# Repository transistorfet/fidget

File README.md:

Fidget - The FPGA Widget
========================

###### *Started January 5, 2023*

This project is an experiment in making a board using a Lattice iCE40 FPGA in a surface mount
package (LQFP-144).  It has bus connectors to allow it to be hooked up to one of the
[Computie](https://jabberwocky.ca/projects/computie/) single board computers, to be used as either a
debug monitor to replace the arduino supervisor, or as a generic expansion device for the computers.
I'd also like to be able to use it more generically as well, for example as a logic analyzer, which
is why it's called a widget.

It needs to have bus transceivers to level convert between the 5V signals of the Computie expansion
bus, and the 3.3V I/O pins of the FPGA.  To save on I/Os, the address and data bus lines are
multiplexed using the level-converting transceivers.  I also added the latches necessary to make a
request on the bus.  Without the latches, the device will only be able to receive bus requests but
not make them.

The basic design of the USB and power supply circuitry was mostly copied from the [TinyFPGA
BX](https://www.crowdsupply.com/tinyfpga/tinyfpga-ax-bx) development board.  I bought one back in
early 2020, and have an environment set up for developing for it.  I was able to reuse the
bootloader and upload utility from that to accelerate the bring-up of this board.  I highly
recommend checking it out, especially since it sounds like they will have more boards for sale soon
in 2023.  It's an excellent affordable open source board which is great for experimenting with
verilog and FPGAs.

The schematics can be seen online
[here](https://github.com/transistorfet/fidget/blob/main/hardware/Fidget/Fidget.pdf) or in KiCAD.

This repository uses submodules, and can be cloned using:
```
git clone --recurse-submodules git@github.com:transistorfet/fidget.git
```

Building the Board
------------------

It was surprisingly easy to build, although my attempts at documenting the soldering of the
transceivers resulted in more mistakes than it was worth.  I had solder bridges on every chip that
required some solder wick, and I had a few chips that were crooked enough that I decided to just use
the hot air rework station to remove them and resolder them.  The FPGA was actually much easier to
solder by comparison.  The other parts I had trouble with were the oscillators, which come in a
module on a tiny circuit board with castellated pins on the edges.  The 3.6864 Mhz one was easy
because the footprint turned out to be way bigger than the chip, but the 16 MHz one was the right
size for the part but with not enough clearance for hand soldering.  In future revisions I'll have
to make the footprint bigger.

I started with the 3.3V regulator and tested it with a bench power supply at 5V to verify that I was
getting 3.3V output, which is used by the transceivers.  I then soldered the transceivers and
latches at once, along with their caps, and tested at the end of that.  I put the SPI flash and
oscillators on and tested those with the bench supply to make sure I was getting signal.  The 16 Mhz
oscillator needed a lot of reworking and desoldering.

With the SPI flash chip in, I programmed it (see below).  I also put the other voltage regulators in
and tested them before soldering the FPGA.  With the all the power good, I put the other LEDs,
buttons on, as well as the FPGA itself with its associated caps.  After checking for shorts, I
tested it to see what would happen.  Surprisingly it worked, with the bootloader slowly blinking one
of the LEDs to indicate it was running, so the configuration I had written to the flash chip was
good.  I then put on the remaining headers which were the last components to solder.

At the end, and between the two days I was assembling, I cleaned the flux off with a toothbrush and
some soap and/or rubbing alcohol.  I then blow dried the board to make sure the water under the
chips was dry before it had a chance to corrode any pins.  It's best to not get the board too hot
when doing this.

I like to use water soluble liquid flux.  The No Clean stuff is much harder to clean up after, but
it doesn't have to be cleaned off, where as the water soluble stuff can corrode the pins if it's not
cleaned off, but works better and is easy to clean.

For soldering, I use a soldering tip that's cone-shaped but cut off at an angle to form a large flat
surface.  It heats the pad on the board better than a round tip, which gives a good solder
connection for SMT components, even though it's wider than individual pins.  The solder mask and
flux make the solder flow well and not bridge.  I have a Quick 861DW hot air rework station for when
I make mistakes, but I only needed to use it twice, once to remove the 3 crooked
transceivers/latches, which probably would have been ok if I had left them, and once to remove the
16 MHz oscillator.

Initializing the Board
----------------------

To load the initial bootloader, I used [spi-flash-programmer](https://github.com/nfd/spi-flash-programmer)
and an [AdaFruit QT Py](https://www.adafruit.com/product/4600) I had laying around, which just
happened to be the most convenient 3.3V Arduino-compatible board I had available, but any 3.3V
Arduino will do.  I uploaded the flash programmer to it, but I needed to adjust the SPI speed
because the default was too high for the long dupont wires I used to connect it to Fidget.

I programmed the SPI chip in circuit before I soldered the FPGA in place, just in case they
interfered, which was a good idea because they did interfere.  With the FPGA in circuit, the RESET
button needs to be held for the duration of SPI programming (preferably for the whole time the
Arduino is connected), or it won't work.

I connected the SCK, SDI, and SDO signals on the Arduino to the SPI Flash header on Fidget, along
with a general purpose I/O (I used A0/D0) connected to the CS pin on the header.  I also connected
power from the QT Py to power the board while programming, which does also power the FPGA and
transceivers, but since the QT Py has the exact same 3.3V regulator I used, as it turns out, which
is capable of 600mA, it has no problem powering the whole board up.

I compiled the [TinyFPGA Bootloader](https://github.com/tinyfpga/TinyFPGA-Bootloader), using a board
configuration based on the BX, but with the device to compile to changed (hx4k-tq144) and pin
assignments changed.  Compiling it with `make` produces a fw.bin file, as well as bootloader_0.bin,
and bootloader_1.bin.

As it turned out, I needed to write fw.bin to the start of the device, even though at the end of
compiling it says to write bootloader_0.bin to 0xa0, and bootloader_1.bin to 0x28000.  Before I put
the chip on, I wrote the two images separately with some zero padding at the start, and for some
reason it still worked when I put the chip on.  I later reprogrammed it once I was able to program
in-circuit after some unrelated problems with a wire not making good connection.

The first 0xa0 bytes of data is actually the boot vector table used by the FPGA itself to locate the
configurations in the remaining part of memory.  It has 5 entries, one for the cold boot
configuration to load at startup, and the remaining 4 for the selectable warm boot configurations.
The TinyFPGA bootloader only uses 2 configurations, the bootloader itself, and the user program.,
and puts the bootloader as the target of all the other entries.  For more info on the boot vectors,
check out [https://umarcor.github.io/warmboot/](https://umarcor.github.io/warmboot/).

The bootloader didn't work at first.  It would raise uncaught exceptions everywhere, but it turned
out to be that it was trying to load meta data and there wasn't any programmed into the SPI Flash.
I didn't know this was needed, and for some reason using the bootloader to program the security page
would say that it worked but would always read back 0xFFs.  I haven't tried putting it in user
memory, which the bootloader also checks for metadata.  I just hacked it to use the default TinyFPGA
BX meta data and it programs just fine.  I'll fix it properly, eventually.

I had some other issues with the blinking led test, where it just wouldn't work, but it turned out
to be that I had the HX1K device still configured, from before I decide to switch to the HX4K.  The
1k device wasn't big enough to house the configuration for the bootloader, which left me kind of
hooped unless I switched.  The 4ks aren't as easily available but I managed to buy a few from
another distributor I don't normally buy from.

Now I can upload configuration through USB using tinyprog and the bootloader!

```sh
python3 spi_flash_programmer_client.py -d /dev/ttyACM2 --io 0 write -f fw.bin -l 0x28000 --pad 0xff
```

Loading through the Bootloader
------------------------------

I currently have the meta data hacked in, but it can be written to the security pages or to an area
of the SPI Flash.  It's in `rtl/TinyFPGA-Bootloader/boards/Fidget/metadata.json`.  With that, it
should recognize the boot loader and upload

From the `rtl/TinyFPGA-Bootloader/programmer`:
```sh
python3 -m tinyprog -p ../../blinking_led/fidget.bin
```

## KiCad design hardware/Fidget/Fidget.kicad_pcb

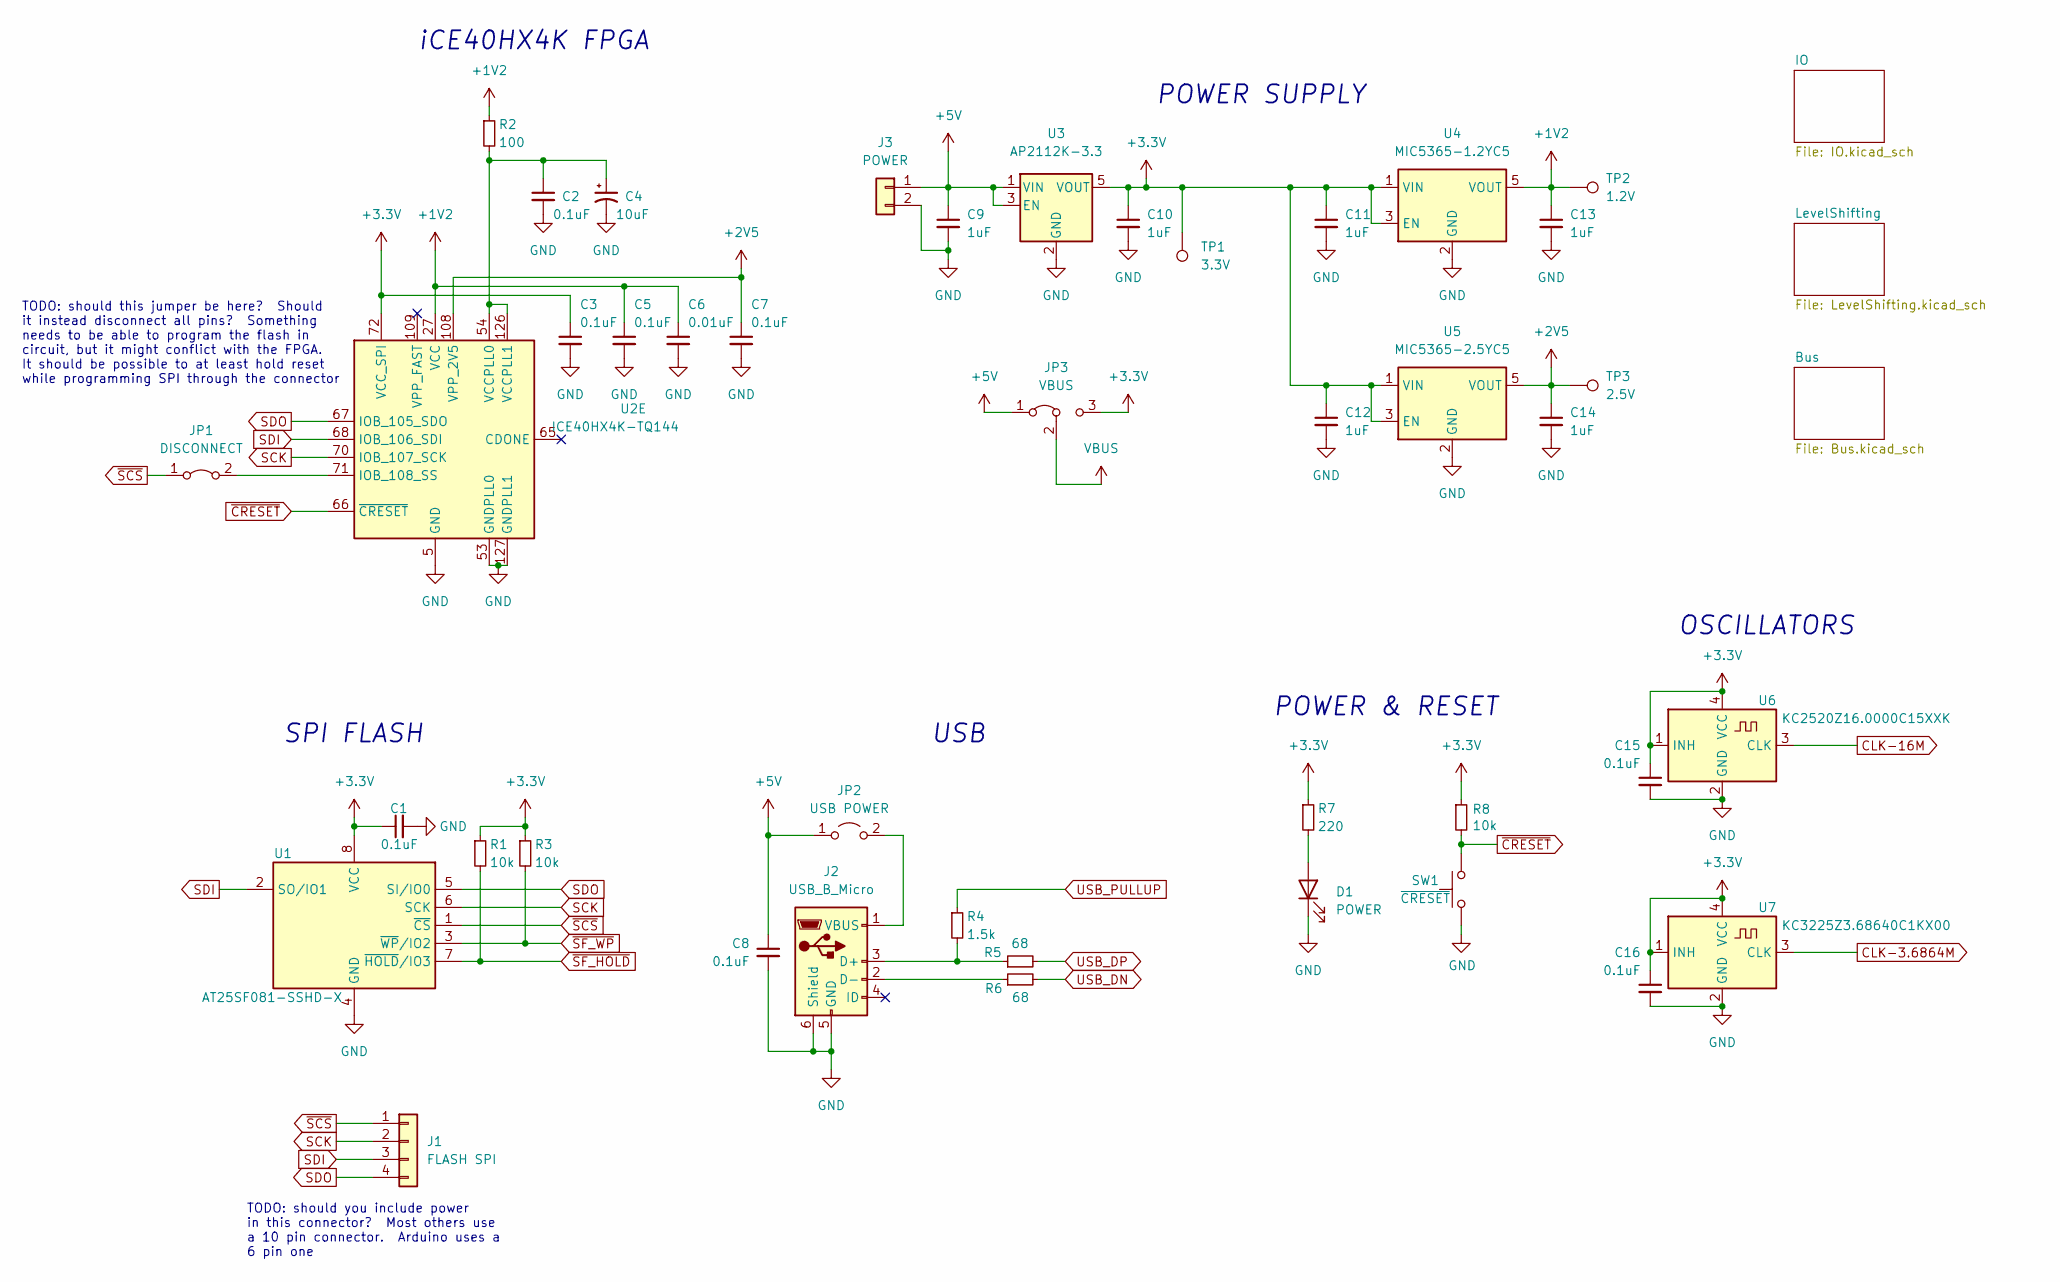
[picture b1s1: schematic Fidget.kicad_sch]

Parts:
C1, C2, C3, C5, C7, C8, C15, C16: 0.1uF; C_0805_2012Metric_Pad1.18x1.45mm_HandSolder
C4: 10uF; C_1206_3216Metric_Pad1.33x1.80mm_HandSolder
C6: 0.01uF; C_0805_2012Metric_Pad1.18x1.45mm_HandSolder
C9, C10, C11, C12, C13, C14: 1uF; C_1206_3216Metric_Pad1.33x1.80mm_HandSolder
D1: POWER
J1: FLASH SPI; PinHeader_1x04_P2.54mm_Vertical
J2: USB_B_Micro; USB_Micro-B_Amphenol_10118194_Horizontal
J3: POWER; PinHeader_1x02_P2.54mm_Vertical
JP1: DISCONNECT; PinHeader_1x02_P2.54mm_Vertical
JP2: USB POWER; PinHeader_1x02_P2.54mm_Vertical
JP3: VBUS; PinHeader_1x03_P2.54mm_Vertical
R1, R3: 10k; R_0805_2012Metric_Pad1.20x1.40mm_HandSolder
R2: 100; R_0805_2012Metric_Pad1.20x1.40mm_HandSolder
R4: 1.5k; R_0805_2012Metric_Pad1.20x1.40mm_HandSolder
R5, R6: 68; R_0805_2012Metric_Pad1.20x1.40mm_HandSolder
R7: 220; R_Axial_DIN0204_L3.6mm_D1.6mm_P5.08mm_Horizontal
R8: 10k; R_Axial_DIN0204_L3.6mm_D1.6mm_P5.08mm_Horizontal
SW1: ~{CRESET}; SW_PUSH_6mm
TP1: 3.3V; TestPoint_THTPad_2.0x2.0mm_Drill1.0mm
TP2: 1.2V; TestPoint_THTPad_2.0x2.0mm_Drill1.0mm
TP3: 2.5V; TestPoint_THTPad_2.0x2.0mm_Drill1.0mm
U1: AT25SF081-SSHD-X; SOIC-8_3.9x4.9mm_P1.27mm
U2: ICE40HX4K-TQ144; TQFP-144_20x20mm_P0.5mm
U3: AP2112K-3.3; SOT-23-5_HandSoldering
U4: MIC5365-1.2YC5; SOT-353_SC-70-5_Handsoldering
U5: MIC5365-2.5YC5; SOT-353_SC-70-5_Handsoldering
U6: KC2520Z16.0000C15XXK; Oscillator_SMD_Kyocera_KC2520Z-4Pin_2.5x2.0mm
U7: KC3225Z3.68640C1KX00; Oscillator_SMD_Kyocera_KC2520Z-4Pin_2.5x2.0mm

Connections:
+1V2: C5.1, C6.1, C13.1, R2.1, TP2.1, U2.27 (VCC), U2.40 (VCC), U2.92 (VCC), U2.111 (VCC), U4.5 (VOUT)
+2V5: C7.1, C14.1, TP3.1, U2.108 (VPP_2V5), U5.5 (VOUT)
+3.3V: C1.1, C3.1, C10.1, C11.1, C12.1, C15.1, C16.1, JP3.3 (B), R1.1, R3.1, R7.1, R8.1, TP1.1, U1.8 (VCC), U2.72 (VCC_SPI), U3.5 (VOUT), U4.1 (VIN), U4.3 (EN), U5.1 (VIN), U5.3 (EN), U6.1 (INH), U6.4 (VCC), U7.1 (INH), U7.4 (VCC); also elsewhere on the board
+5V: C8.1, C9.1, J3.1, JP2.1 (A), JP3.1 (A), U3.1 (VIN), U3.3 (EN); also elsewhere on the board
CLK-3.6864M: U7.3 (CLK); also elsewhere on the board
CLK-16M: U6.3 (CLK); also elsewhere on the board
GND: C1.2, C2.2, C3.2, C4.2, C5.2, C6.2, C7.2, C8.2, C9.2, C10.2, C11.2, C12.2, C13.2, C14.2, C15.2, C16.2, D1.1 (K), J2.5 (GND), J2.6 (Shield), J3.2, SW1.1, U1.4 (GND), U2.5 (GND), U2.13 (GND), U2.14 (GND), U2.53 (GNDPLL0), U2.59 (GND), U2.69 (GND), U2.86 (GND), U2.103 (GND), U2.127 (GNDPLL1), U2.132 (GND), U2.140 (GND), U3.2 (GND), U4.2 (GND), U5.2 (GND), U6.2 (GND), U7.2 (GND); also elsewhere on the board
unnamed: C2.1, C4.1, R2.2, U2.54 (VCCPLL0), U2.126 (VCCPLL1)
unnamed: D1.2 (A), R7.2
unnamed: J2.1 (VBUS), JP2.2 (B)
unnamed: J2.2 (D-), R6.1
unnamed: J2.3 (D+), R4.2, R5.1
unnamed: JP1.2 (B), U2.71 (IOB_108_SS)
SCK: J1.2, U1.6 (SCK), U2.70 (IOB_107_SCK)
SDI: J1.3, U1.2 (SO/IO1), U2.68 (IOB_106_SDI)
SDO: J1.4, U1.5 (SI/IO0), U2.67 (IOB_105_SDO)
USB_DN: R6.2; also elsewhere on the board
USB_DP: R5.2; also elsewhere on the board
USB_PULLUP: R4.1; also elsewhere on the board
VBUS: JP3.2 (C); also elsewhere on the board
~CRESET: R8.2, SW1.2, U2.66 (~CRESET)
~SCS: J1.1, JP1.1 (A), U1.1 (~CS)
~SF_HOLD: R1.2, U1.7 (~HOLD/IO3); also elsewhere on the board
~SF_WP: R3.2, U1.3 (~WP/IO2); also elsewhere on the board

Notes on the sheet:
OSCILLATORS
POWER & RESET
USB
iCE40HX4K FPGA
TODO: should you include power in this connector? Most others use a 10 pin connector. Arduino uses a 6 pin one
TODO: should this jumper be here? Should it instead disconnect all pins? Something needs to be able to program the flash in circuit, but it might conflict with the FPGA. It should be possible to at least hold reset while programming SPI through the connector
SPI FLASH
POWER SUPPLY

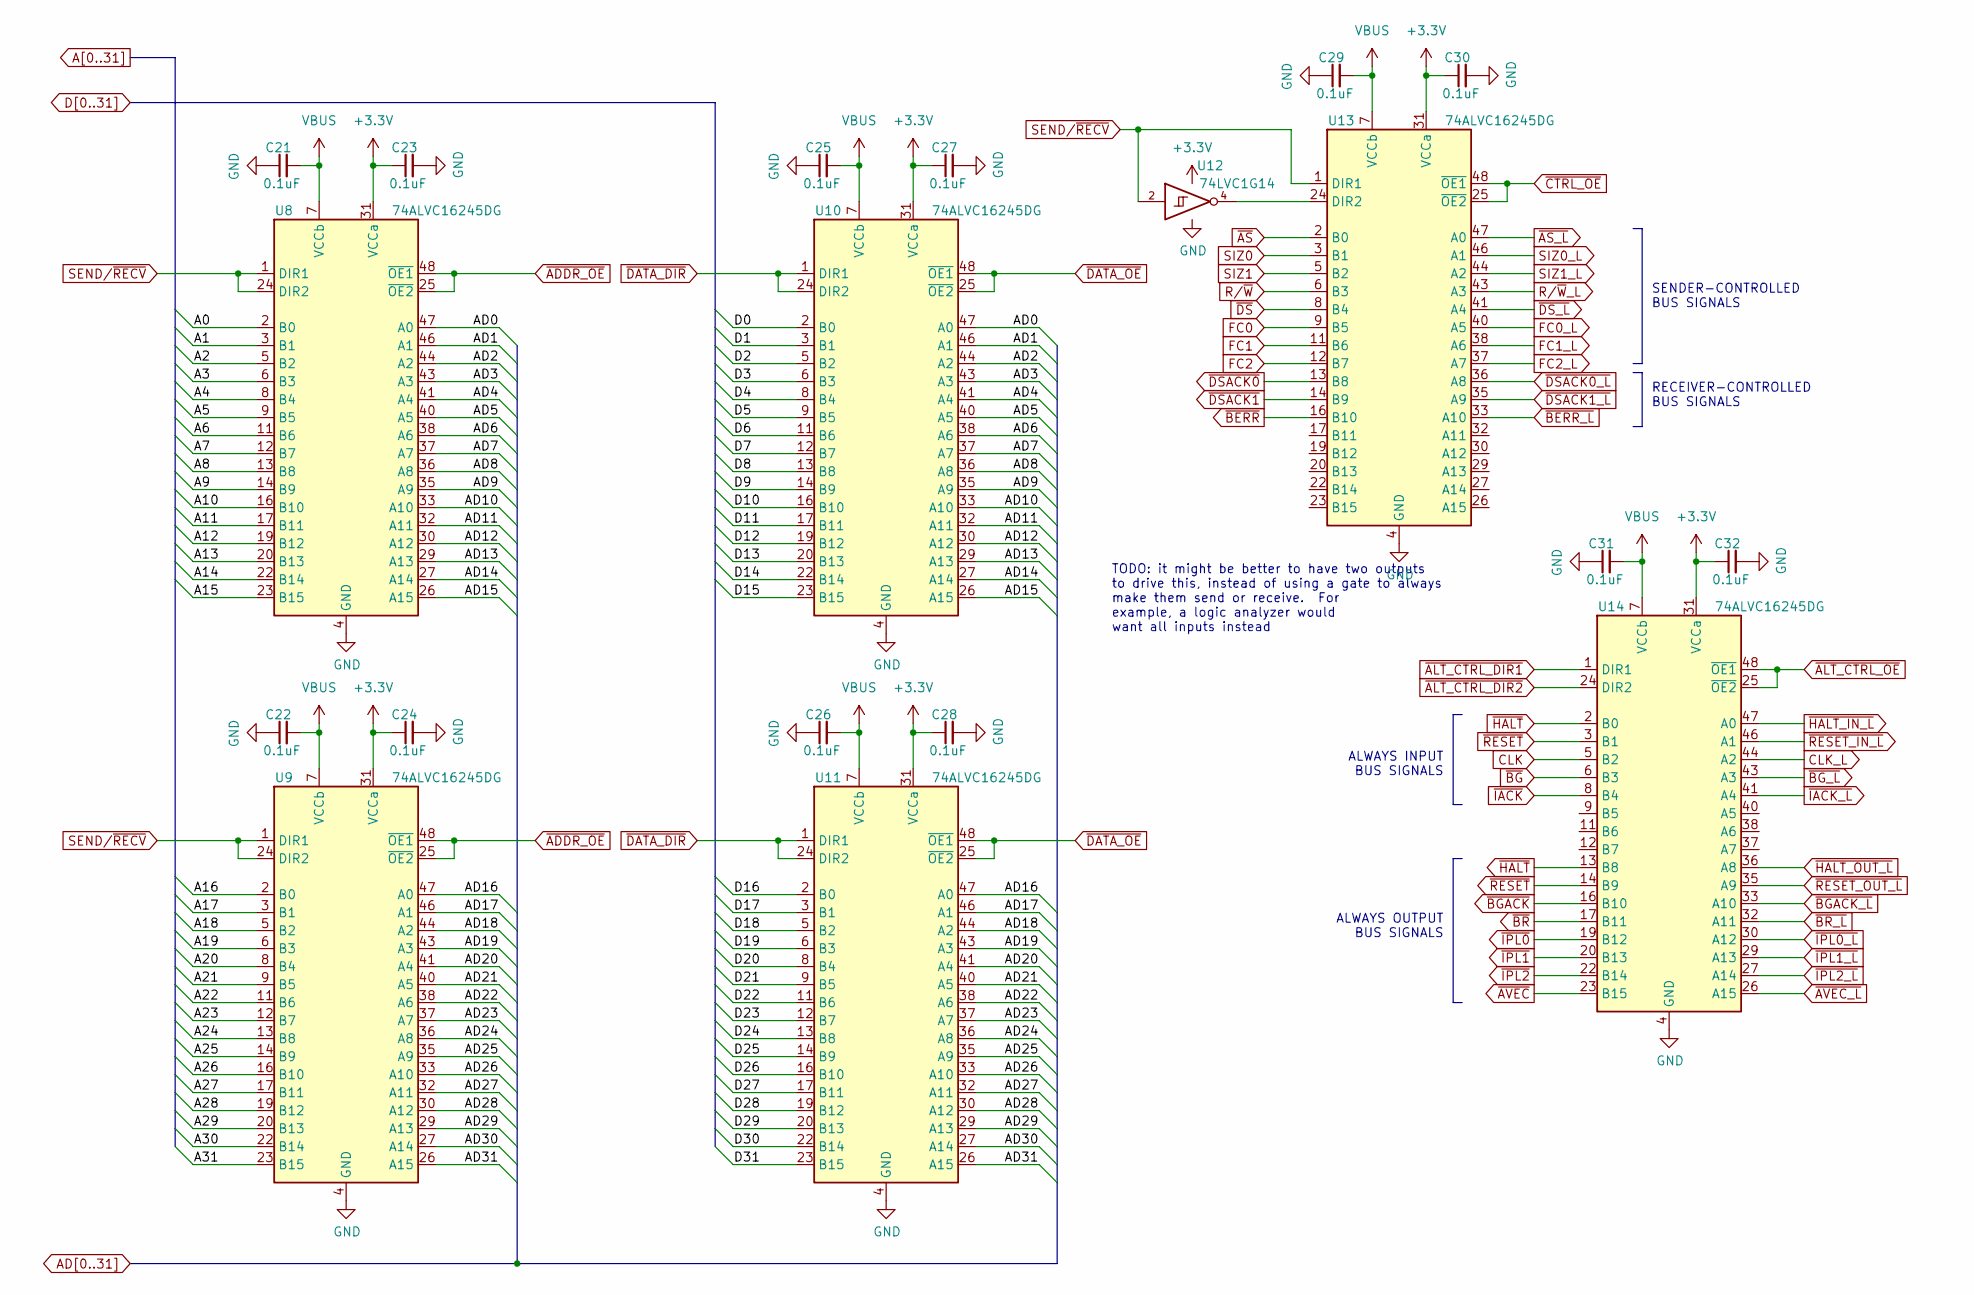
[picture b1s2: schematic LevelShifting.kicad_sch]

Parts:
C21, C22, C23, C24, C25, C26, C27, C28, C29, C30, C31, C32: 0.1uF; C_0805_2012Metric_Pad1.18x1.45mm_HandSolder
U8, U9, U10, U11, U13, U14: 74ALVC16245DG; TSSOP-48_6.1x12.5mm_P0.5mm
U12: 74LVC1G14; SOT-353_SC-70-5_Handsoldering

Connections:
+3.3V: C23.1, C24.1, C27.1, C28.1, C30.1, C32.1, U8.31 (VCCa), U8.42 (VCCa), U9.31 (VCCa), U9.42 (VCCa), U10.31 (VCCa), U10.42 (VCCa), U11.31 (VCCa), U11.42 (VCCa), U12.5 (VCC), U13.31 (VCCa), U13.42 (VCCa), U14.31 (VCCa), U14.42 (VCCa); also elsewhere on the board
A0: U8.2 (B0); also elsewhere on the board
A1: U8.3 (B1); also elsewhere on the board
A2: U8.5 (B2); also elsewhere on the board
A3: U8.6 (B3); also elsewhere on the board
A4: U8.8 (B4); also elsewhere on the board
A5: U8.9 (B5); also elsewhere on the board
A6: U8.11 (B6); also elsewhere on the board
A7: U8.12 (B7); also elsewhere on the board
A8: U8.13 (B8); also elsewhere on the board
A9: U8.14 (B9); also elsewhere on the board
A10: U8.16 (B10); also elsewhere on the board
A11: U8.17 (B11); also elsewhere on the board
A12: U8.19 (B12); also elsewhere on the board
A13: U8.20 (B13); also elsewhere on the board
A14: U8.22 (B14); also elsewhere on the board
A15: U8.23 (B15); also elsewhere on the board
A16: U9.2 (B0); also elsewhere on the board
A17: U9.3 (B1); also elsewhere on the board
A18: U9.5 (B2); also elsewhere on the board
A19: U9.6 (B3); also elsewhere on the board
A20: U9.8 (B4); also elsewhere on the board
A21: U9.9 (B5); also elsewhere on the board
A22: U9.11 (B6); also elsewhere on the board
A23: U9.12 (B7); also elsewhere on the board
A24: U9.13 (B8); also elsewhere on the board
A25: U9.14 (B9); also elsewhere on the board
A26: U9.16 (B10); also elsewhere on the board
A27: U9.17 (B11); also elsewhere on the board
A28: U9.19 (B12); also elsewhere on the board
A29: U9.20 (B13); also elsewhere on the board
A30: U9.22 (B14); also elsewhere on the board
A31: U9.23 (B15); also elsewhere on the board
AD0: U8.47 (A0), U10.47 (A0); also elsewhere on the board
AD1: U8.46 (A1), U10.46 (A1); also elsewhere on the board
AD2: U8.44 (A2), U10.44 (A2); also elsewhere on the board
AD3: U8.43 (A3), U10.43 (A3); also elsewhere on the board
AD4: U8.41 (A4), U10.41 (A4); also elsewhere on the board
AD5: U8.40 (A5), U10.40 (A5); also elsewhere on the board
AD6: U8.38 (A6), U10.38 (A6); also elsewhere on the board
AD7: U8.37 (A7), U10.37 (A7); also elsewhere on the board
AD8: U8.36 (A8), U10.36 (A8); also elsewhere on the board
AD9: U8.35 (A9), U10.35 (A9); also elsewhere on the board
AD10: U8.33 (A10), U10.33 (A10); also elsewhere on the board
AD11: U8.32 (A11), U10.32 (A11); also elsewhere on the board
AD12: U8.30 (A12), U10.30 (A12); also elsewhere on the board
AD13: U8.29 (A13), U10.29 (A13); also elsewhere on the board
AD14: U8.27 (A14), U10.27 (A14); also elsewhere on the board
AD15: U8.26 (A15), U10.26 (A15); also elsewhere on the board
AD16: U9.47 (A0), U11.47 (A0); also elsewhere on the board
AD17: U9.46 (A1), U11.46 (A1); also elsewhere on the board
AD18: U9.44 (A2), U11.44 (A2); also elsewhere on the board
AD19: U9.43 (A3), U11.43 (A3); also elsewhere on the board
AD20: U9.41 (A4), U11.41 (A4); also elsewhere on the board
AD21: U9.40 (A5), U11.40 (A5); also elsewhere on the board
AD22: U9.38 (A6), U11.38 (A6); also elsewhere on the board
AD23: U9.37 (A7), U11.37 (A7); also elsewhere on the board
AD24: U9.36 (A8), U11.36 (A8); also elsewhere on the board
AD25: U9.35 (A9), U11.35 (A9); also elsewhere on the board
AD26: U9.33 (A10), U11.33 (A10); also elsewhere on the board
AD27: U9.32 (A11), U11.32 (A11); also elsewhere on the board
AD28: U9.30 (A12), U11.30 (A12); also elsewhere on the board
AD29: U9.29 (A13), U11.29 (A13); also elsewhere on the board
AD30: U9.27 (A14), U11.27 (A14); also elsewhere on the board
AD31: U9.26 (A15), U11.26 (A15); also elsewhere on the board
CLK: U14.5 (B2); also elsewhere on the board
CLK_L: U14.44 (A2); also elsewhere on the board
D0: U10.2 (B0); also elsewhere on the board
D1: U10.3 (B1); also elsewhere on the board
D2: U10.5 (B2); also elsewhere on the board
D3: U10.6 (B3); also elsewhere on the board
D4: U10.8 (B4); also elsewhere on the board
D5: U10.9 (B5); also elsewhere on the board
D6: U10.11 (B6); also elsewhere on the board
D7: U10.12 (B7); also elsewhere on the board
D8: U10.13 (B8); also elsewhere on the board
D9: U10.14 (B9); also elsewhere on the board
D10: U10.16 (B10); also elsewhere on the board
D11: U10.17 (B11); also elsewhere on the board
D12: U10.19 (B12); also elsewhere on the board
D13: U10.20 (B13); also elsewhere on the board
D14: U10.22 (B14); also elsewhere on the board
D15: U10.23 (B15); also elsewhere on the board
D16: U11.2 (B0); also elsewhere on the board
D17: U11.3 (B1); also elsewhere on the board
D18: U11.5 (B2); also elsewhere on the board
D19: U11.6 (B3); also elsewhere on the board
D20: U11.8 (B4); also elsewhere on the board
D21: U11.9 (B5); also elsewhere on the board
D22: U11.11 (B6); also elsewhere on the board
D23: U11.12 (B7); also elsewhere on the board
D24: U11.13 (B8); also elsewhere on the board
D25: U11.14 (B9); also elsewhere on the board
D26: U11.16 (B10); also elsewhere on the board
D27: U11.17 (B11); also elsewhere on the board
D28: U11.19 (B12); also elsewhere on the board
D29: U11.20 (B13); also elsewhere on the board
D30: U11.22 (B14); also elsewhere on the board
D31: U11.23 (B15); also elsewhere on the board
FC0: U13.9 (B5); also elsewhere on the board
FC0_L: U13.40 (A5); also elsewhere on the board
FC1: U13.11 (B6); also elsewhere on the board
FC1_L: U13.38 (A6); also elsewhere on the board
FC2: U13.12 (B7); also elsewhere on the board
FC2_L: U13.37 (A7); also elsewhere on the board
GND: C21.1, C22.1, C23.2, C24.2, C25.1, C26.1, C27.2, C28.2, C29.1, C30.2, C31.1, C32.2, U8.4 (GND), U8.10 (GND), U8.15 (GND), U8.21 (GND), U8.28 (GND), U8.34 (GND), U8.39 (GND), U8.45 (GND), U9.4 (GND), U9.10 (GND), U9.15 (GND), U9.21 (GND), U9.28 (GND), U9.34 (GND), U9.39 (GND), U9.45 (GND), U10.4 (GND), U10.10 (GND), U10.15 (GND), U10.21 (GND), U10.28 (GND), U10.34 (GND), U10.39 (GND), U10.45 (GND), U11.4 (GND), U11.10 (GND), U11.15 (GND), U11.21 (GND), U11.28 (GND), U11.34 (GND), U11.39 (GND), U11.45 (GND), U12.3 (GND), U13.4 (GND), U13.10 (GND), U13.15 (GND), U13.21 (GND), U13.28 (GND), U13.34 (GND), U13.39 (GND), U13.45 (GND), U14.4 (GND), U14.10 (GND), U14.15 (GND), U14.21 (GND), U14.28 (GND), U14.34 (GND), U14.39 (GND), U14.45 (GND); also elsewhere on the board
unnamed: U12.4, U13.24 (DIR2)
R/~W: U13.6 (B3); also elsewhere on the board
R/~W_L: U13.43 (A3); also elsewhere on the board
SEND/~RECV: U8.1 (DIR1), U8.24 (DIR2), U9.1 (DIR1), U9.24 (DIR2), U12.2, U13.1 (DIR1); also elsewhere on the board
SIZ0: U13.3 (B1); also elsewhere on the board
SIZ0_L: U13.46 (A1); also elsewhere on the board
SIZ1: U13.5 (B2); also elsewhere on the board
SIZ1_L: U13.44 (A2); also elsewhere on the board
VBUS: C21.2, C22.2, C25.2, C26.2, C29.2, C31.2, U8.7 (VCCb), U8.18 (VCCb), U9.7 (VCCb), U9.18 (VCCb), U10.7 (VCCb), U10.18 (VCCb), U11.7 (VCCb), U11.18 (VCCb), U13.7 (VCCb), U13.18 (VCCb), U14.7 (VCCb), U14.18 (VCCb); also elsewhere on the board
~ADDR_OE: U8.25 (~OE2), U8.48 (~OE1), U9.25 (~OE2), U9.48 (~OE1); also elsewhere on the board
~ALT_CTRL_DIR1: U14.1 (DIR1); also elsewhere on the board
~ALT_CTRL_DIR2: U14.24 (DIR2); also elsewhere on the board
~ALT_CTRL_OE: U14.25 (~OE2), U14.48 (~OE1); also elsewhere on the board
~AS_L: U13.47 (A0); also elsewhere on the board
~AS: U13.2 (B0); also elsewhere on the board
~AVEC_L: U14.26 (A15); also elsewhere on the board
~AVEC: U14.23 (B15); also elsewhere on the board
~BERR_L: U13.33 (A10); also elsewhere on the board
~BERR: U13.16 (B10); also elsewhere on the board
~BGACK_L: U14.33 (A10); also elsewhere on the board
~BGACK: U14.16 (B10); also elsewhere on the board
~BG_L: U14.43 (A3); also elsewhere on the board
~BG: U14.6 (B3); also elsewhere on the board
~BR_L: U14.32 (A11); also elsewhere on the board
~BR: U14.17 (B11); also elsewhere on the board
~CTRL_OE: U13.25 (~OE2), U13.48 (~OE1); also elsewhere on the board
~DATA_DIR: U10.1 (DIR1), U10.24 (DIR2), U11.1 (DIR1), U11.24 (DIR2); also elsewhere on the board
~DATA_OE: U10.25 (~OE2), U10.48 (~OE1), U11.25 (~OE2), U11.48 (~OE1); also elsewhere on the board
~DSACK0_L: U13.36 (A8); also elsewhere on the board
~DSACK0: U13.13 (B8); also elsewhere on the board
~DSACK1_L: U13.35 (A9); also elsewhere on the board
~DSACK1: U13.14 (B9); also elsewhere on the board
~DS_L: U13.41 (A4); also elsewhere on the board
~DS: U13.8 (B4); also elsewhere on the board
~HALT_IN_L: U14.47 (A0); also elsewhere on the board
~HALT_OUT_L: U14.36 (A8); also elsewhere on the board
~HALT: U14.2 (B0), U14.13 (B8); also elsewhere on the board
~IACK_L: U14.41 (A4); also elsewhere on the board
~IACK: U14.8 (B4); also elsewhere on the board
~IPL0_L: U14.30 (A12); also elsewhere on the board
~IPL0: U14.19 (B12); also elsewhere on the board
~IPL1_L: U14.29 (A13); also elsewhere on the board
~IPL1: U14.20 (B13); also elsewhere on the board
~IPL2_L: U14.27 (A14); also elsewhere on the board
~IPL2: U14.22 (B14); also elsewhere on the board
~RESET_IN_L: U14.46 (A1); also elsewhere on the board
~RESET_OUT_L: U14.35 (A9); also elsewhere on the board
~RESET: U14.3 (B1), U14.14 (B9); also elsewhere on the board

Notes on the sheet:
TODO: it might be better to have two outputs to drive this, instead of using a gate to always make them send or receive. For example, a logic analyzer would want all inputs instead
SENDER-CONTROLLED BUS SIGNALS
ALWAYS INPUT BUS SIGNALS
ALWAYS OUTPUT BUS SIGNALS
RECEIVER-CONTROLLED BUS SIGNALS

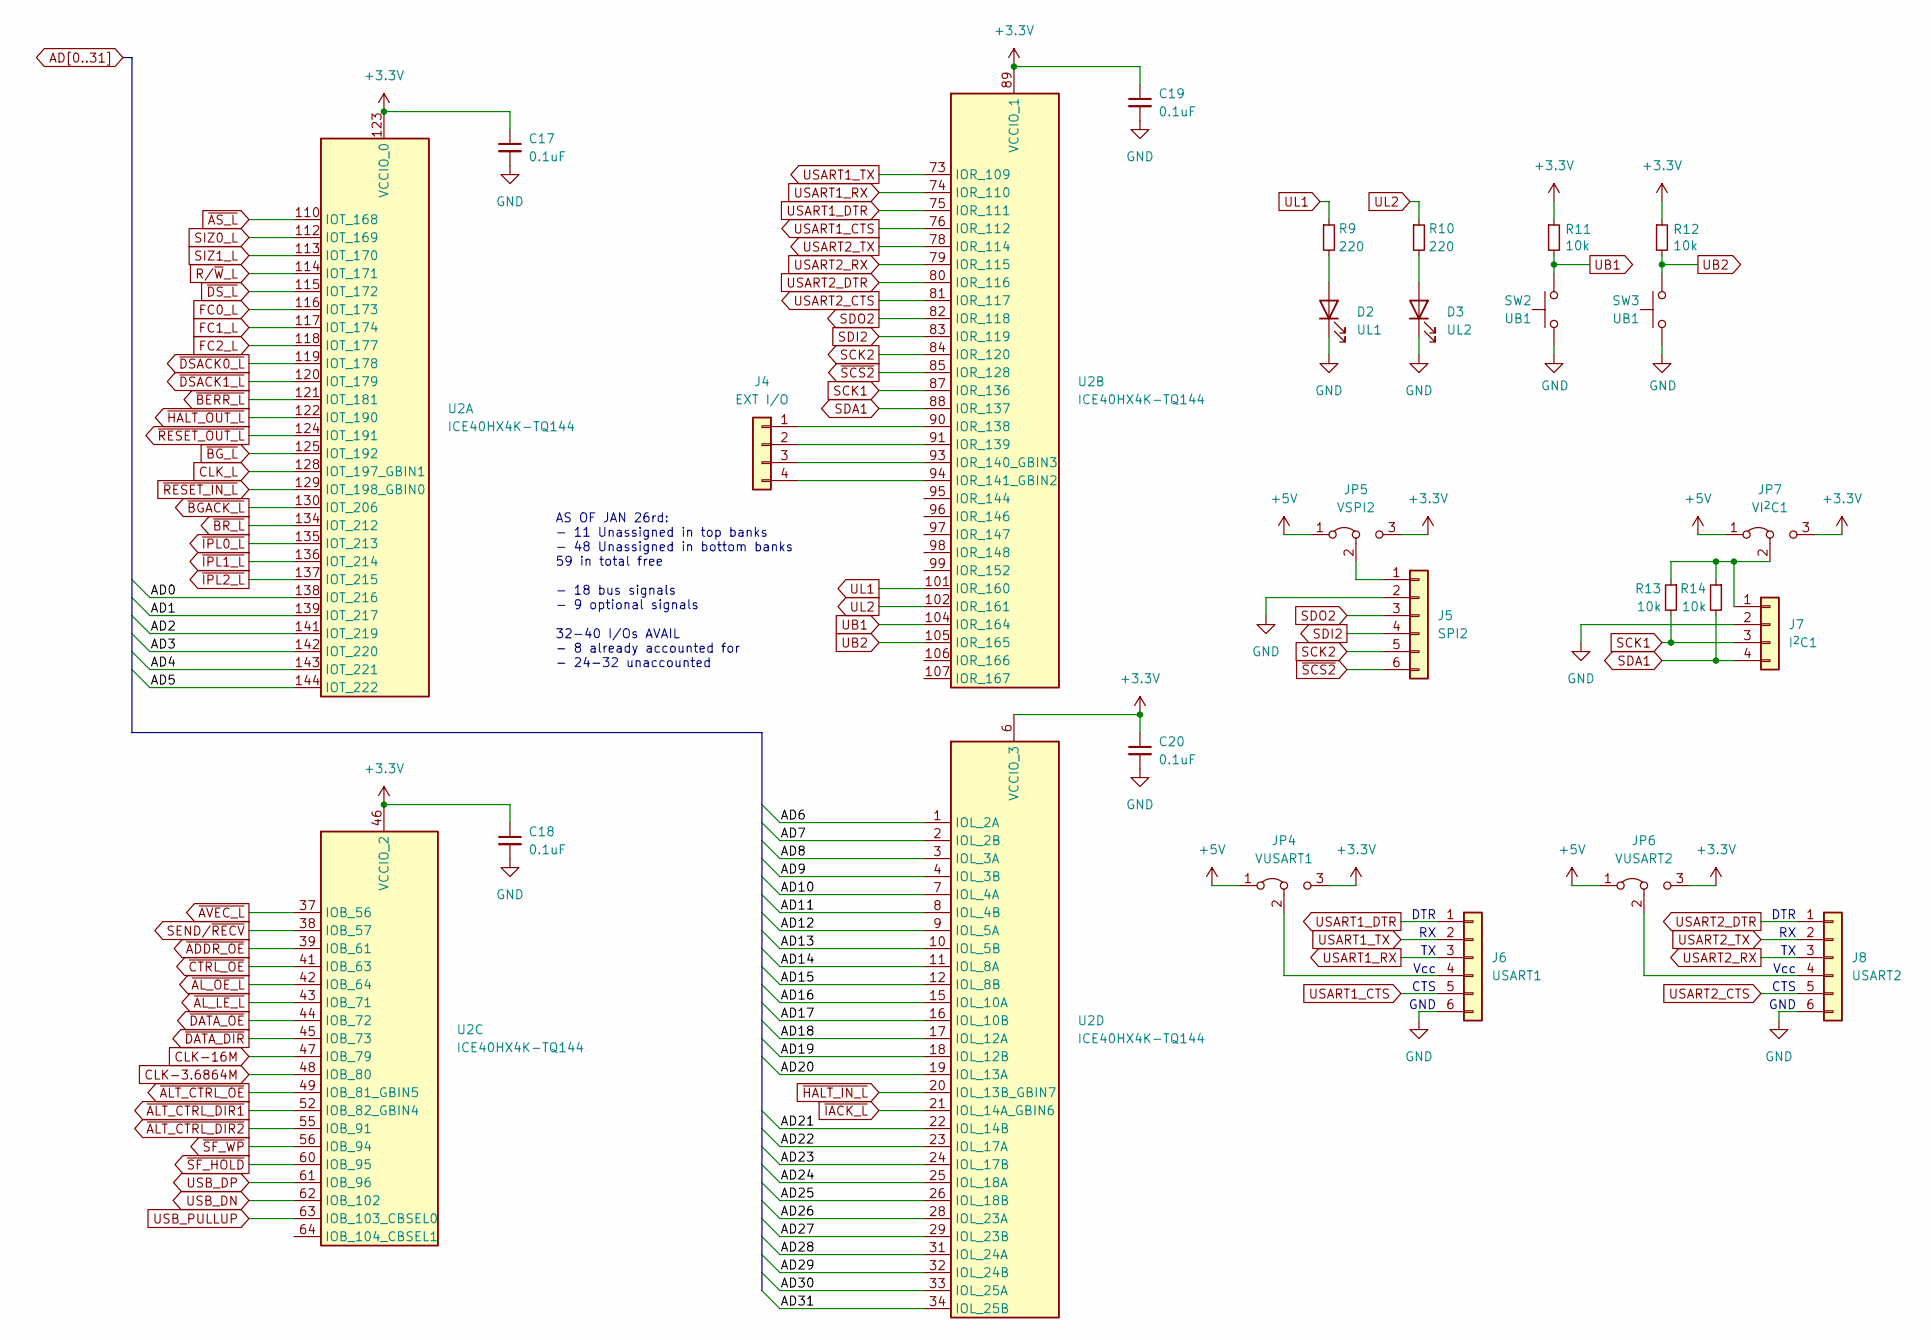
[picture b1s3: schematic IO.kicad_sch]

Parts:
C17, C18, C19, C20: 0.1uF; C_0805_2012Metric_Pad1.18x1.45mm_HandSolder
D2: UL1
D3: UL2
J4: EXT I/O; PinHeader_1x04_P2.54mm_Vertical
J5: SPI2; PinHeader_1x06_P2.54mm_Vertical
J6: USART1; PinHeader_1x06_P2.54mm_Vertical
J7: I^{2}C1; PinHeader_1x04_P2.54mm_Vertical
J8: USART2; PinHeader_1x06_P2.54mm_Vertical
JP4: VUSART1; PinHeader_1x03_P2.54mm_Vertical
JP5: VSPI2; PinHeader_1x03_P2.54mm_Vertical
JP6: VUSART2; PinHeader_1x03_P2.54mm_Vertical
JP7: VI^{2}C1; PinHeader_1x03_P2.54mm_Vertical
R9, R10: 220; R_Axial_DIN0204_L3.6mm_D1.6mm_P5.08mm_Horizontal
R11, R12, R13, R14: 10k; R_Axial_DIN0204_L3.6mm_D1.6mm_P5.08mm_Horizontal
SW2, SW3: UB1; SW_PUSH_6mm
U2: ICE40HX4K-TQ144; TQFP-144_20x20mm_P0.5mm

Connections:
+3.3V: C17.1, C18.1, C19.1, C20.1, JP4.3 (B), JP5.3 (B), JP6.3 (B), JP7.3 (B), R11.1, R12.1, U2.6 (VCCIO_3), U2.30 (VCCIO_3), U2.46 (VCCIO_2), U2.57 (VCCIO_2), U2.89 (VCCIO_1), U2.100 (VCCIO_1), U2.123 (VCCIO_0), U2.131 (VCCIO_0); also elsewhere on the board
+5V: JP4.1 (A), JP5.1 (A), JP6.1 (A), JP7.1 (A); also elsewhere on the board
AD0: U2.138 (IOT_216); also elsewhere on the board
AD1: U2.139 (IOT_217); also elsewhere on the board
AD2: U2.141 (IOT_219); also elsewhere on the board
AD3: U2.142 (IOT_220); also elsewhere on the board
AD4: U2.143 (IOT_221); also elsewhere on the board
AD5: U2.144 (IOT_222); also elsewhere on the board
AD6: U2.1 (IOL_2A); also elsewhere on the board
AD7: U2.2 (IOL_2B); also elsewhere on the board
AD8: U2.3 (IOL_3A); also elsewhere on the board
AD9: U2.4 (IOL_3B); also elsewhere on the board
AD10: U2.7 (IOL_4A); also elsewhere on the board
AD11: U2.8 (IOL_4B); also elsewhere on the board
AD12: U2.9 (IOL_5A); also elsewhere on the board
AD13: U2.10 (IOL_5B); also elsewhere on the board
AD14: U2.11 (IOL_8A); also elsewhere on the board
AD15: U2.12 (IOL_8B); also elsewhere on the board
AD16: U2.15 (IOL_10A); also elsewhere on the board
AD17: U2.16 (IOL_10B); also elsewhere on the board
AD18: U2.17 (IOL_12A); also elsewhere on the board
AD19: U2.18 (IOL_12B); also elsewhere on the board
AD20: U2.19 (IOL_13A); also elsewhere on the board
AD21: U2.22 (IOL_14B); also elsewhere on the board
AD22: U2.23 (IOL_17A); also elsewhere on the board
AD23: U2.24 (IOL_17B); also elsewhere on the board
AD24: U2.25 (IOL_18A); also elsewhere on the board
AD25: U2.26 (IOL_18B); also elsewhere on the board
AD26: U2.28 (IOL_23A); also elsewhere on the board
AD27: U2.29 (IOL_23B); also elsewhere on the board
AD28: U2.31 (IOL_24A); also elsewhere on the board
AD29: U2.32 (IOL_24B); also elsewhere on the board
AD30: U2.33 (IOL_25A); also elsewhere on the board
AD31: U2.34 (IOL_25B); also elsewhere on the board
CLK-3.6864M: U2.48 (IOB_80); also elsewhere on the board
CLK-16M: U2.47 (IOB_79); also elsewhere on the board
CLK_L: U2.128 (IOT_197_GBIN1); also elsewhere on the board
FC0_L: U2.116 (IOT_173); also elsewhere on the board
FC1_L: U2.117 (IOT_174); also elsewhere on the board
FC2_L: U2.118 (IOT_177); also elsewhere on the board
GND: C17.2, C18.2, C19.2, C20.2, D2.1 (K), D3.1 (K), J5.2, J6.6, J7.2, J8.6, SW2.1, SW3.1; also elsewhere on the board
unnamed: D2.2 (A), R9.2
unnamed: D3.2 (A), R10.2
unnamed: J4.1, U2.90 (IOR_138)
unnamed: J4.2, U2.91 (IOR_139)
unnamed: J4.3, U2.93 (IOR_140_GBIN3)
unnamed: J4.4, U2.94 (IOR_141_GBIN2)
unnamed: J5.1, JP5.2 (C)
unnamed: J6.4, JP4.2 (C)
unnamed: J7.1, JP7.2 (C), R13.1, R14.1
unnamed: J8.4, JP6.2 (C)
R/~W_L: U2.114 (IOT_171); also elsewhere on the board
SCK1: J7.3, R13.2, U2.87 (IOR_136)
SCK2: J5.5, U2.84 (IOR_120)
SDA1: J7.4, R14.2, U2.88 (IOR_137)
SDI2: J5.4, U2.83 (IOR_119)
SDO2: J5.3, U2.82 (IOR_118)
SEND/~RECV: U2.38 (IOB_57); also elsewhere on the board
SIZ0_L: U2.112 (IOT_169); also elsewhere on the board
SIZ1_L: U2.113 (IOT_170); also elsewhere on the board
UB1: R11.2, SW2.2, U2.104 (IOR_164)
UB2: R12.2, SW3.2, U2.105 (IOR_165)
UL1: R9.1, U2.101 (IOR_160)
UL2: R10.1, U2.102 (IOR_161)
USART1_CTS: J6.5, U2.76 (IOR_112)
USART1_DTR: J6.1, U2.75 (IOR_111)
USART1_RX: J6.3, U2.74 (IOR_110)
USART1_TX: J6.2, U2.73 (IOR_109)
USART2_CTS: J8.5, U2.81 (IOR_117)
USART2_DTR: J8.1, U2.80 (IOR_116)
USART2_RX: J8.3, U2.79 (IOR_115)
USART2_TX: J8.2, U2.78 (IOR_114)
USB_DN: U2.62 (IOB_102); also elsewhere on the board
USB_DP: U2.61 (IOB_96); also elsewhere on the board
USB_PULLUP: U2.63 (IOB_103_CBSEL0); also elsewhere on the board
~ADDR_OE: U2.39 (IOB_61); also elsewhere on the board
~ALT_CTRL_DIR1: U2.52 (IOB_82_GBIN4); also elsewhere on the board
~ALT_CTRL_DIR2: U2.55 (IOB_91); also elsewhere on the board
~ALT_CTRL_OE: U2.49 (IOB_81_GBIN5); also elsewhere on the board
~AL_LE_L: U2.43 (IOB_71); also elsewhere on the board
~AL_OE_L: U2.42 (IOB_64); also elsewhere on the board
~AS_L: U2.110 (IOT_168); also elsewhere on the board
~AVEC_L: U2.37 (IOB_56); also elsewhere on the board
~BERR_L: U2.121 (IOT_181); also elsewhere on the board
~BGACK_L: U2.130 (IOT_206); also elsewhere on the board
~BG_L: U2.125 (IOT_192); also elsewhere on the board
~BR_L: U2.134 (IOT_212); also elsewhere on the board
~CTRL_OE: U2.41 (IOB_63); also elsewhere on the board
~DATA_DIR: U2.45 (IOB_73); also elsewhere on the board
~DATA_OE: U2.44 (IOB_72); also elsewhere on the board
~DSACK0_L: U2.119 (IOT_178); also elsewhere on the board
~DSACK1_L: U2.120 (IOT_179); also elsewhere on the board
~DS_L: U2.115 (IOT_172); also elsewhere on the board
~HALT_IN_L: U2.20 (IOL_13B_GBIN7); also elsewhere on the board
~HALT_OUT_L: U2.122 (IOT_190); also elsewhere on the board
~IACK_L: U2.21 (IOL_14A_GBIN6); also elsewhere on the board
~IPL0_L: U2.135 (IOT_213); also elsewhere on the board
~IPL1_L: U2.136 (IOT_214); also elsewhere on the board
~IPL2_L: U2.137 (IOT_215); also elsewhere on the board
~RESET_IN_L: U2.129 (IOT_198_GBIN0); also elsewhere on the board
~RESET_OUT_L: U2.124 (IOT_191); also elsewhere on the board
~SCS2: J5.6, U2.85 (IOR_128)
~SF_HOLD: U2.60 (IOB_95); also elsewhere on the board
~SF_WP: U2.56 (IOB_94); also elsewhere on the board

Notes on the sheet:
DTR
GND
CTS
Vcc
AS OF JAN 26rd: - 11 Unassigned in top banks - 48 Unassigned in bottom banks 59 in total free - 18 bus signals - 9 optional signals 32-40 I/Os AVAIL - 8 already accounted for - 24-32 unaccounted
